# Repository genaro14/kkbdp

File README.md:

# KKBDP
## Kiss Keyboard Project
+ clone like this:  
```bash
 $ git clone --recurse-submodules -j8 https://github.com/genaro14/kkbdp
```
+ Uploading the CONTRA Firmware, asuming that this Repo was cloned to home folder
```bash
$ ~/.arduino15/packages/arduino/tools/avrdude/6.3.0-arduino17/bin/avrdude -C~/.arduino15/packages/arduino/tools/avrdude/6.3.0-arduino17/etc/avrdude.conf -v -patmega32u4 -cavr109 -P/dev/ttyACM0 -b57600 -D -Uflash:w:~/keyboard/tmk_keyboard/keyboard/contra/contra.hex:i
```

## Tool
+ Tutorial Kicad: https://github.com/ruiqimao/keyboard-pcb-guide#setting-up
+ Layout Editor: http://www.keyboard-layout-editor.com
+ Plate: http://builder.swillkb.com/
+ Case: https://www.thingiverse.com/thing:4402730
+ Firmware: https://github.com/qmk/qmk_firmware/tree/master/keyboards/planck

### Contra:
http://www.40percent.club/2018/03/contra.html
https://github.com/ai03-2725/Contra
### Contra Plates
https://github.com/ai03-2725/ContraPlates

### Objective 1: 40% Ortholinear
+ Include as much Open Source environment as possible.
+ Single sided PCB(ultra low cost, etching at home possible)
+ Cherry Mx(or clones) only
+ Standard THT diodes
+ Arduino Pro micro(for availability)
+ Kicad desing

### Status:
1: Seems possible

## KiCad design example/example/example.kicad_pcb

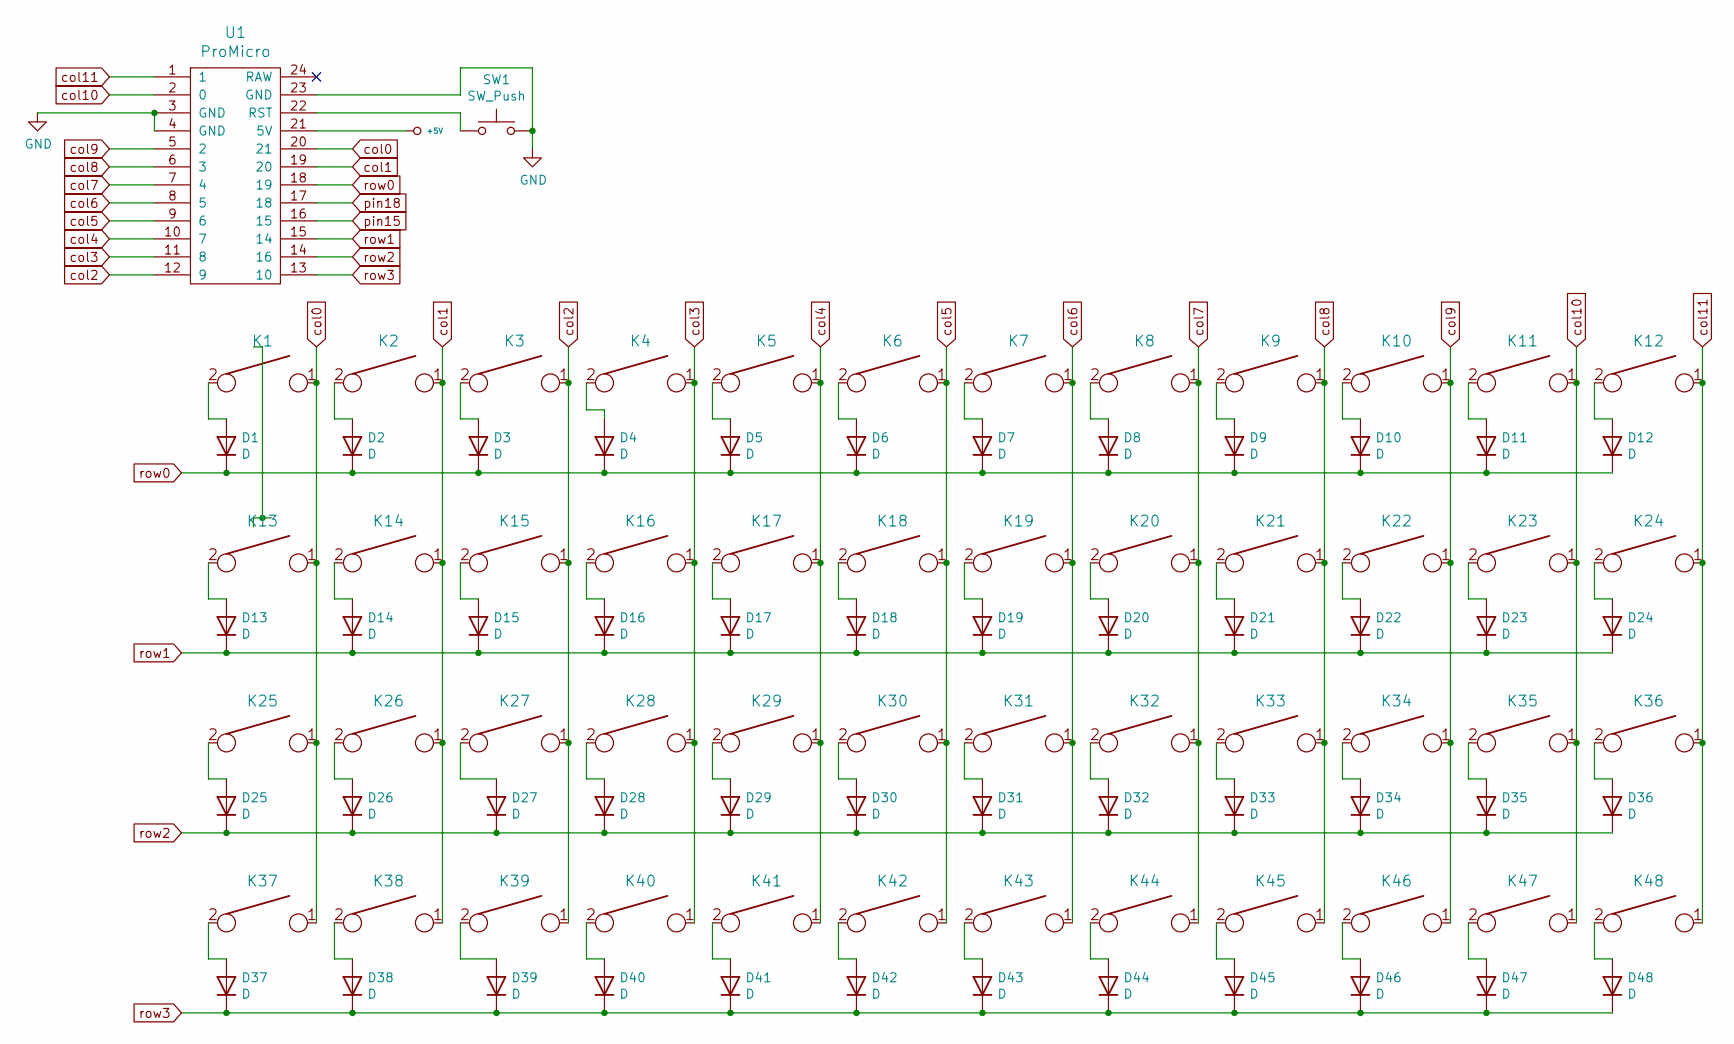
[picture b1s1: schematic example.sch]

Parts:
D1, D2, D3, D4, D5, D6, D7, D8, D9, D10, D11, D12, D13, D14, D15, D16, D17, D18, D19, D20, D21, D22, D23, D24, D25, D26, D27, D28, D29, D30, D31, D32, D33, D34, D35, D36, D37, D38, D39, D40, D41, D42, D43, D44, D45, D46, D47, D48: D; D_DO-35_SOD27_P7.62mm_Horizontal
K1, K2, K3, K4, K5, K6, K7, K8, K9, K10, K11, K12, K13, K14, K15, K16, K17, K18, K19, K20, K21, K22, K23, K24, K25, K26, K27, K28, K29, K30, K31, K32, K33, K34, K35, K36, K37, K38, K39, K40, K41, K42, K43, K44, K45, K46, K47, K48: KEYSW; SW_Cherry_MX_1.00u_Plate
SW1: SW_Push; PinHeader_2x01_P2.54mm_Vertical
U1: ProMicro; pro_micro

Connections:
+5V: U1.21 (5V)
GND: SW1.2, U1.3 (GND), U1.4 (GND), U1.23 (GND)
unnamed: D1.2 (A), K1.2
unnamed: D2.2 (A), K2.2
unnamed: D3.2 (A), K3.2
unnamed: D4.2 (A), K4.2
unnamed: D5.2 (A), K5.2
unnamed: D6.2 (A), K6.2
unnamed: D7.2 (A), K7.2
unnamed: D8.2 (A), K8.2
unnamed: D9.2 (A), K9.2
unnamed: D10.2 (A), K10.2
unnamed: D11.2 (A), K11.2
unnamed: D12.2 (A), K12.2
unnamed: D13.2 (A), K13.2
unnamed: D14.2 (A), K14.2
unnamed: D15.2 (A), K15.2
unnamed: D16.2 (A), K16.2
unnamed: D17.2 (A), K17.2
unnamed: D18.2 (A), K18.2
unnamed: D19.2 (A), K19.2
unnamed: D20.2 (A), K20.2
unnamed: D21.2 (A), K21.2
unnamed: D22.2 (A), K22.2
unnamed: D23.2 (A), K23.2
unnamed: D24.2 (A), K24.2
unnamed: D25.2 (A), K25.2
unnamed: D26.2 (A), K26.2
unnamed: D27.2 (A), K27.2
unnamed: D28.2 (A), K28.2
unnamed: D29.2 (A), K29.2
unnamed: D30.2 (A), K30.2
unnamed: D31.2 (A), K31.2
unnamed: D32.2 (A), K32.2
unnamed: D33.2 (A), K33.2
unnamed: D34.2 (A), K34.2
unnamed: D35.2 (A), K35.2
unnamed: D36.2 (A), K36.2
unnamed: D37.2 (A), K37.2
unnamed: D38.2 (A), K38.2
unnamed: D39.2 (A), K39.2
unnamed: D40.2 (A), K40.2
unnamed: D41.2 (A), K41.2
unnamed: D42.2 (A), K42.2
unnamed: D43.2 (A), K43.2
unnamed: D44.2 (A), K44.2
unnamed: D45.2 (A), K45.2
unnamed: D46.2 (A), K46.2
unnamed: D47.2 (A), K47.2
unnamed: D48.2 (A), K48.2
unnamed: SW1.1, U1.22 (RST)
col0: K1.1, K13.1, K25.1, K37.1, U1.20 (21)
col1: K2.1, K14.1, K26.1, K38.1, U1.19 (20)
col2: K3.1, K15.1, K27.1, K39.1, U1.12 (9)
col3: K4.1, K16.1, K28.1, K40.1, U1.11 (8)
col4: K5.1, K17.1, K29.1, K41.1, U1.10 (7)
col5: K6.1, K18.1, K30.1, K42.1, U1.9 (6)
col6: K7.1, K19.1, K31.1, K43.1, U1.8 (5)
col7: K8.1, K20.1, K32.1, K44.1, U1.7 (4)
col8: K9.1, K21.1, K33.1, K45.1, U1.6 (3)
col9: K10.1, K22.1, K34.1, K46.1, U1.5 (2)
col10: K11.1, K23.1, K35.1, K47.1, U1.2 (0)
col11: K12.1, K24.1, K36.1, K48.1, U1.1
pin15: U1.16 (15)
pin18: U1.17 (18)
row0: D1.1 (K), D2.1 (K), D3.1 (K), D4.1 (K), D5.1 (K), D6.1 (K), D7.1 (K), D8.1 (K), D9.1 (K), D10.1 (K), D11.1 (K), D12.1 (K), U1.18 (19)
row1: D13.1 (K), D14.1 (K), D15.1 (K), D16.1 (K), D17.1 (K), D18.1 (K), D19.1 (K), D20.1 (K), D21.1 (K), D22.1 (K), D23.1 (K), D24.1 (K), U1.15 (14)
row2: D25.1 (K), D26.1 (K), D27.1 (K), D28.1 (K), D29.1 (K), D30.1 (K), D31.1 (K), D32.1 (K), D33.1 (K), D34.1 (K), D35.1 (K), D36.1 (K), U1.14 (16)
row3: D37.1 (K), D38.1 (K), D39.1 (K), D40.1 (K), D41.1 (K), D42.1 (K), D43.1 (K), D44.1 (K), D45.1 (K), D46.1 (K), D47.1 (K), D48.1 (K), U1.13 (10)

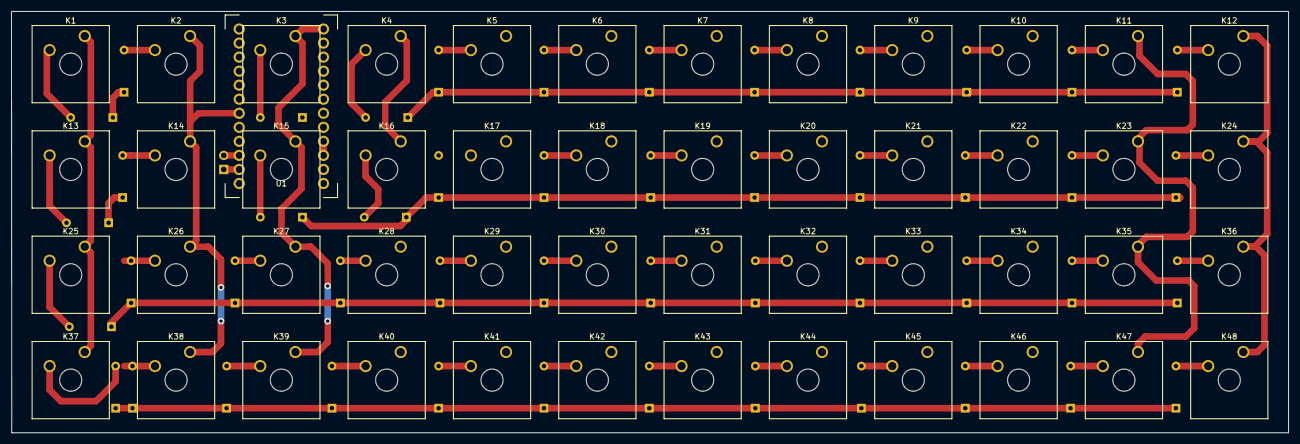
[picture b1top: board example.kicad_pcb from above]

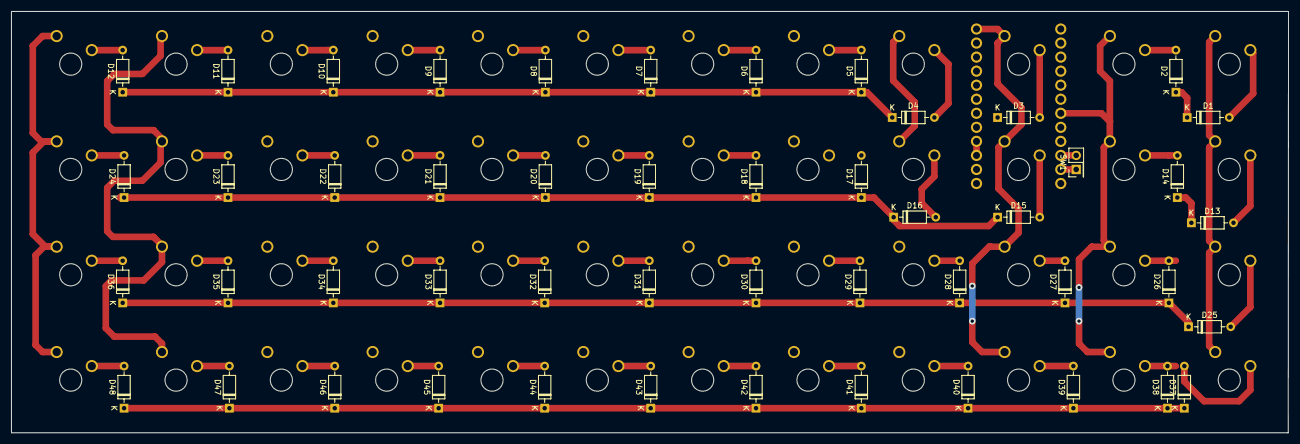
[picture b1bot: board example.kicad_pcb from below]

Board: 2 copper layers, 231.0 x 76.2 mm, 98 parts (49 on the bottom side), 66 nets.

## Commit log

2020-10-17 Repo init 17/10/2020
2020-10-17 Submodules fix
2020-10-17 Submodules for firmware and upload example
2020-10-17 Readme adding
2020-10-17 Readme code higlighting
2020-10-18 Update .gitmodules
    adding libs
2020-10-23 Kicad template 4x12
2020-10-23 Kicad template 4x12 not wired
2020-10-23 Remove 3d libs
2020-10-27 state of Art
